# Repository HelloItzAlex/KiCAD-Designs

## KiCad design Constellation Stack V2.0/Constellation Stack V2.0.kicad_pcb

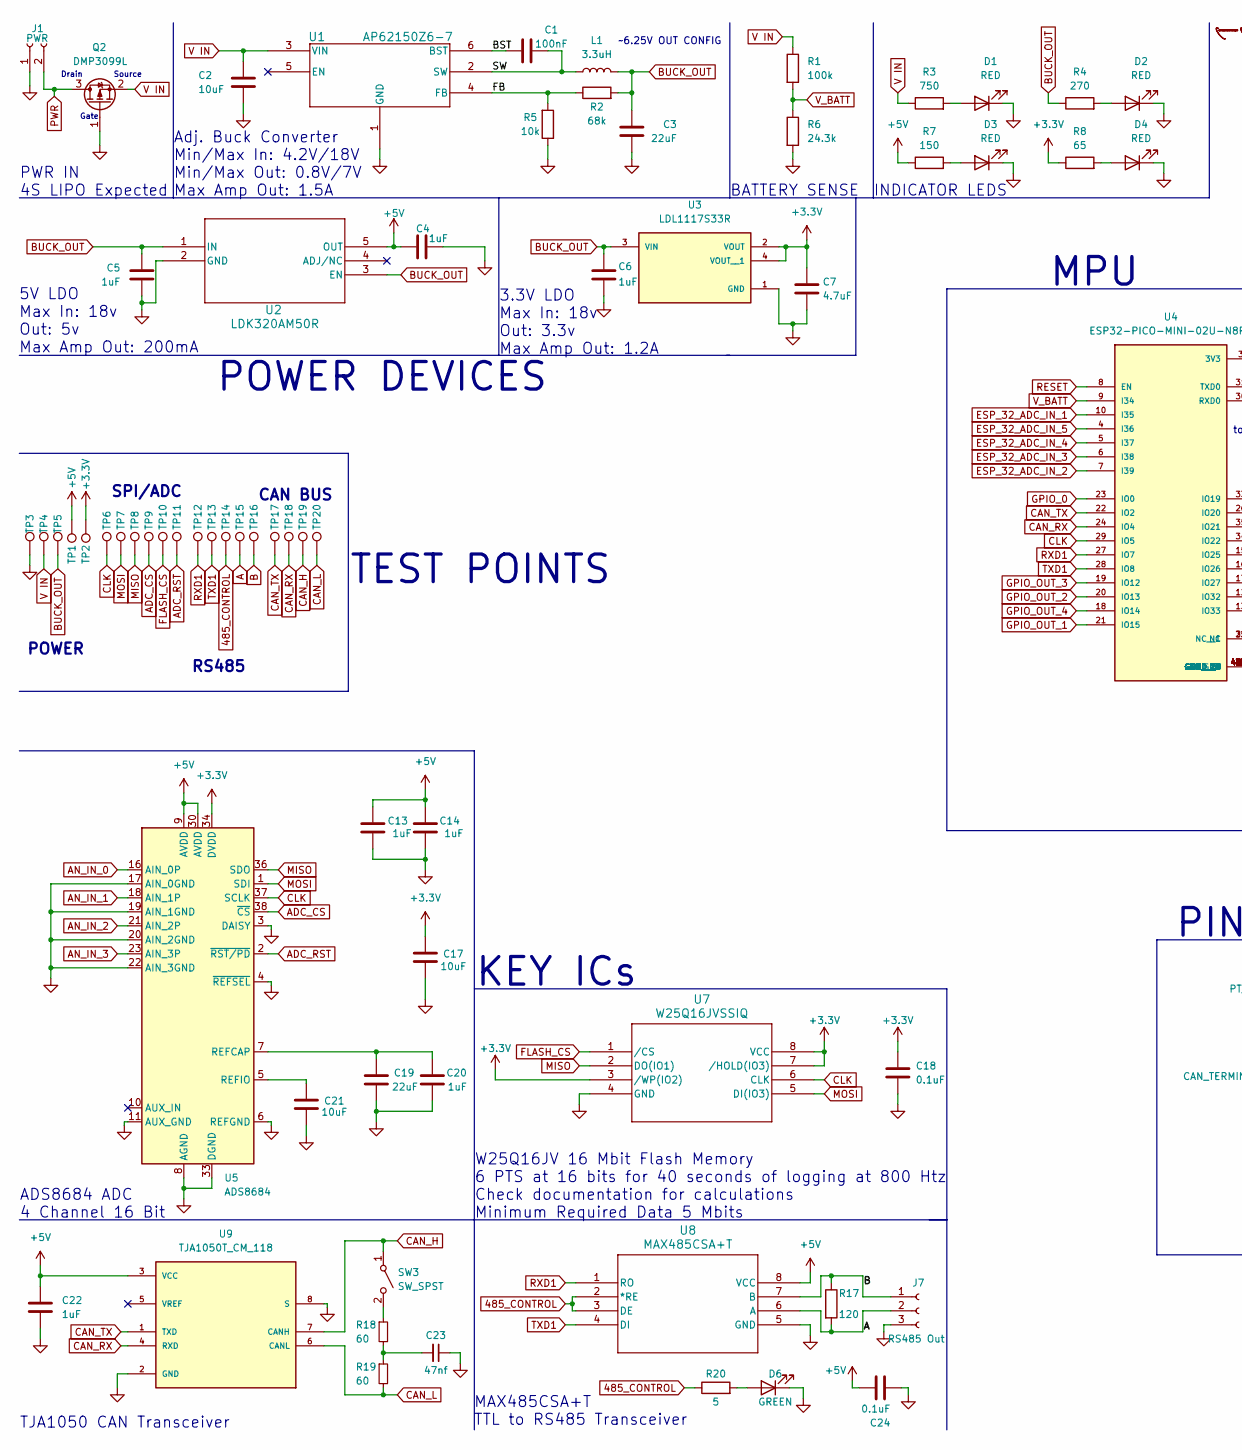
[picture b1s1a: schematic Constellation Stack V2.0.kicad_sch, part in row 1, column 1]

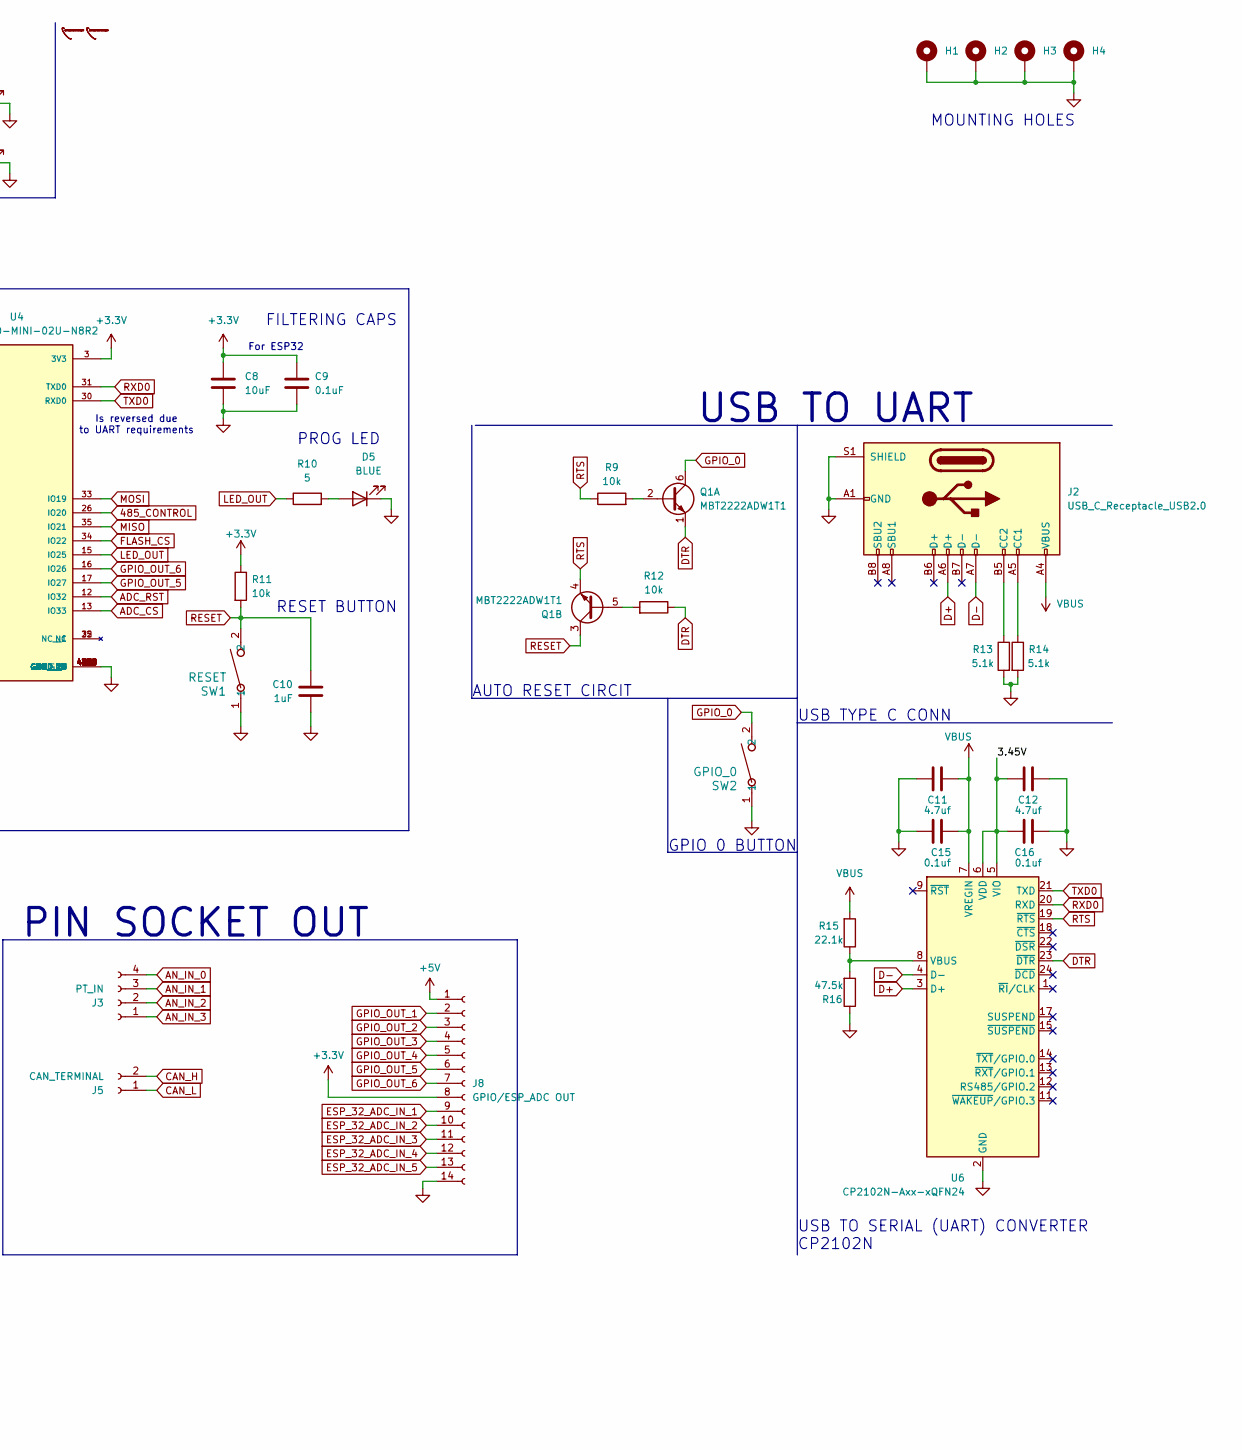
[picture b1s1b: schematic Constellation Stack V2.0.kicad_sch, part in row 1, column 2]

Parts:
C1: 100nF; C_0603_1608Metric
C2, C8, C17: 10uF; C_0805_2012Metric
C3: 22uF; C_0603_1608Metric
C4, C10, C13, C14, C20, C22: 1uF; C_0603_1608Metric
C5, C6: 1uF; C_0805_2012Metric
C7: 4.7uF; C_0603_1608Metric
C9, C18, C24: 0.1uF; C_0603_1608Metric
C11, C12: 4.7uf; C_0603_1608Metric
C15, C16: 0.1uf; C_0603_1608Metric
C19: 22uF; C_1210_3225Metric
C21: 10uF; C_0603_1608Metric
C23: 47nf; C_0603_1608Metric
D1, D2, D3, D4: RED; LED_0603_1608Metric
D5: BLUE; LED_0603_1608Metric
D6: GREEN; LED_0603_1608Metric
H1, H2, H3, H4: MountingHole_Pad; MountingHole_3.2mm_M3_DIN965_Pad
J1: PWR; PinSocket_1x02_P2.54mm_Vertical
J2: USB_C_Receptacle_USB2.0; USB_C_Receptacle_HCTL_HC-TYPE-C-16P-01A
J3: PT_IN; PinSocket_1x04_P2.54mm_Vertical
J5: CAN_TERMINAL; PinSocket_1x02_P2.54mm_Vertical
J7: RS485 Out; PinSocket_1x03_P2.54mm_Vertical
J8: GPIO/ESP_ADC OUT; PinSocket_1x14_P2.54mm_Vertical
L1: 3.3uH; L_1008_2520Metric
Q1: MBT2222ADW1T1; SOT-363_SC-70-6
Q2: DMP3099L; SOT-23-3
R1: 100k; R_0603_1608Metric
R2: 68k; R_0603_1608Metric
R3: 750; R_0603_1608Metric
R4: 270; R_0603_1608Metric
R5, R9, R11, R12: 10k; R_0603_1608Metric
R6: 24.3k; R_0603_1608Metric
R7: 150; R_0603_1608Metric
R8: 65; R_0603_1608Metric
R10, R20: 5; R_0603_1608Metric
R13, R14: 5.1k; R_0603_1608Metric
R15: 22.1k; R_0603_1608Metric
R16: 47.5k; R_0603_1608Metric
R17: 120; R_0805_2012Metric
R18, R19: 60; R_0805_2012Metric
SW1: RESET; SW_PTS636_CNK
SW2: GPIO_0; SW_PTS636_CNK
SW3: SW_SPST; SolderJumper-2_P1.3mm_Open_RoundedPad1.0x1.5mm
TP1, TP2, TP3, TP4, TP5, TP6, TP7, TP8, TP9, TP10, TP11, TP12, TP13, TP14, TP15, TP16, TP17, TP18, TP19, TP20: TestPoint; TestPoint_Loop_D2.60mm_Drill1.6mm_Beaded
U1: AP62150Z6-7; TSOT-23-6
U2: LDK320AM50R; SC-74A-5_1.55x2.9mm_P0.95mm
U3: LDL1117S33R; SOT-223; PARTREV 7
U4: ESP32-PICO-MINI-02U-N8R2; MODULE_ESP32-PICO-MINI-02U-N8R2; PARTREV v1.1
U5: ADS8684; TSSOP-38_4.4x9.7mm_P0.5mm
U6: CP2102N-Axx-xQFN24; QFN-24-1EP_4x4mm_P0.5mm_EP2.7x2.7mm
U7: W25Q16JVSSIQ; SOIC-8_5.275x5.275mm_P1.27mm
U8: MAX485CSA+T; SOIC-8_3.9x4.9mm_P1.27mm
U9: TJA1050T_CM_118; SOIC-8_3.9x4.9mm_P1.27mm; PARTREV 4

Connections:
485_CONTROL: R20.1, TP14.1, U4.26 (IO20), U8.2 (*RE), U8.3 (DE)
+3.3V: C7.1, C8.1, C9.1, C17.2, C18.1, J8.8, R8.1, R11.1, TP2.1, U3.2 (VOUT), U3.4 (VOUT__1), U4.3 (3V3), U5.34 (DVDD), U7.3 (/WP(IO2)), U7.7 (/HOLD(IO3)), U7.8 (VCC)
+5V: C4.1, C13.2, C14.2, C22.1, C24.1, J8.1, R7.1, TP1.1, U2.5 (OUT), U5.9 (AVDD), U5.30 (AVDD), U8.8 (VCC), U9.3 (VCC)
/3.45V: C12.1, C16.1, U6.5 (VIO), U6.6 (VDD)
/BST: C1.1, U1.6 (BST)
/FB: R2.1, R5.2, U1.4 (FB)
/SW: C1.2, L1.1, U1.2 (SW)
A: J7.2, R17.2, TP15.1, U8.6 (A)
ADC_CS: TP9.1, U4.13 (IO33), U5.38 (~CS)
ADC_RST: TP11.1, U4.12 (IO32), U5.2 (~RST/PD)
AN_IN_0: J3.4, U5.16 (AIN_0P)
AN_IN_1: J3.3, U5.18 (AIN_1P)
AN_IN_2: J3.2, U5.21 (AIN_2P)
AN_IN_3: J3.1, U5.23 (AIN_3P)
B: J7.1, R17.1, TP16.1, U8.7 (B)
BUCK_OUT: C3.1, C5.1, C6.1, L1.2, R2.2, R4.1, TP5.1, U2.1 (IN), U2.3 (EN), U3.3 (VIN)
CAN_H: J5.2, SW3.1 (A), TP19.1, U9.7 (CANH)
CAN_L: J5.1, R19.2, TP20.1, U9.6 (CANL)
CAN_RX: TP18.1, U4.24 (IO4), U9.4 (RXD)
CAN_TX: TP17.1, U4.22 (IO2), U9.1 (TXD)
CLK: TP6.1, U4.29 (IO5), U5.37 (SCLK), U7.6 (CLK)
D+: J2.A6 (D+), U6.3 (D+)
D-: J2.A7 (D-), U6.4 (D-)
DTR: Q1.1 (E1), R12.1, U6.23 (~DTR)
ESP_32_ADC_IN_1: J8.9, U4.10 (I35)
ESP_32_ADC_IN_2: J8.10, U4.7 (I39)
ESP_32_ADC_IN_3: J8.11, U4.6 (I38)
ESP_32_ADC_IN_4: J8.12, U4.5 (I37)
ESP_32_ADC_IN_5: J8.13, U4.4 (I36)
FLASH_CS: TP10.1, U4.34 (IO22), U7.1 (/CS)
GND: C2.2, C3.2, C4.2, C5.2, C6.2, C7.2, C8.2, C9.2, C10.2, C11.2, C12.2, C13.1, C14.1, C15.2, C16.2, C17.1, C18.2, C19.1, C20.1, C21.2, C22.2, C23.1, C24.2, D1.1 (K), D2.1 (K), D3.1 (K), D4.1 (K), D5.1 (K), D6.1 (K), H1.1, H2.1, H3.1, H4.1, J1.1, J2.A1 (GND), J2.A12 (GND), J2.B1 (GND), J2.B12 (GND), J2.S1 (SHIELD), J7.3, J8.14, Q2.1 (G), R5.1, R6.2, R13.2, R14.2, R16.1, SW1.1, SW2.1, TP3.1, U1.1 (GND), U2.2 (GND), U3.1 (GND), U4.1 (GND), U4.2 (GND__1), U4.11 (GND__2), U4.14 (GND__3), U4.36 (GND__4), U4.37 (GND__5), U4.38 (GND__6), U4.39 (GND__7), U4.40 (GND__8), U4.41 (GND__9), U4.42 (GND__10), U4.43 (GND__11), U4.44 (GND__12), U4.45 (GND__13), U4.46 (GND__14), U4.47 (GND__15), U4.48 (GND__16), U4.49_1 (GND__17), U4.49_2 (GND__18), U4.49_3 (GND__19), U4.49_4 (GND__20), U4.49_5 (GND__21), U4.49_6 (GND__22), U4.49_7 (GND__23), U4.49_8 (GND__24), U4.49_9 (GND__25), U4.50 (GND__26), U4.51 (GND__27), U4.52 (GND__28), U4.53 (GND__29), U5.3 (DAISY), U5.4 (~REFSEL), U5.6 (REFGND), U5.8 (AGND), U5.11 (AUX_GND), U5.17 (AIN_0GND), U5.19 (AIN_1GND), U5.20 (AIN_2GND), U5.22 (AIN_3GND), U5.28 (AGND), U5.29 (AGND), U5.31 (AGND), U5.32 (AGND), U5.33 (DGND), U6.2 (GND), U6.25 (GND), U7.4 (GND), U8.5 (GND), U9.2 (GND), U9.8 (S)
GPIO_0: Q1.6 (C1), SW2.2, U4.23 (IO0)
GPIO_OUT_1: J8.2, U4.21 (IO15)
GPIO_OUT_2: J8.3, U4.20 (IO13)
GPIO_OUT_3: J8.4, U4.19 (IO12)
GPIO_OUT_4: J8.5, U4.18 (IO14)
GPIO_OUT_5: J8.6, U4.17 (IO27)
GPIO_OUT_6: J8.7, U4.16 (IO26)
LED_OUT: R10.1, U4.15 (IO25)
MISO: TP8.1, U4.35 (IO21), U5.36 (SDO), U7.2 (DO(IO1))
MOSI: TP7.1, U4.33 (IO19), U5.1 (SDI), U7.5 (DI(IO3))
unnamed: C23.2, R18.2, R19.1
unnamed: D1.2 (A), R3.2
unnamed: D2.2 (A), R4.2
unnamed: D3.2 (A), R7.2
unnamed: D4.2 (A), R8.2
unnamed: D5.2 (A), R10.2
unnamed: D6.2 (A), R20.2
unnamed: J2.A5 (CC1), R14.1
unnamed: J2.B5 (CC2), R13.1
unnamed: Q1.2 (B1), R9.2
unnamed: Q1.5 (B2), R12.2
unnamed: R18.1, SW3.2 (B)
unnamed: C19.2, C20.2, U5.7 (REFCAP)
unnamed: C21.1, U5.5 (REFIO)
unnamed: R15.1, R16.2, U6.8 (VBUS)
PWR: J1.2, Q2.3 (D)
RESET: C10.1, Q1.3 (C2), R11.2, SW1.2, U4.8 (EN)
RTS: Q1.4 (E2), R9.1, U6.19 (~RTS)
RXD0: U4.31 (TXD0), U6.20 (RXD)
RXD1: TP12.1, U4.27 (IO7), U8.1 (RO)
TXD0: U4.30 (RXD0), U6.21 (TXD)
TXD1: TP13.1, U4.28 (IO8), U8.4 (DI)
V IN: C2.1, Q2.2 (S), R1.1, R3.1, TP4.1, U1.3 (VIN)
VBUS: C11.1, C15.1, J2.A4 (VBUS), J2.A9 (VBUS), J2.B4 (VBUS), J2.B9 (VBUS), R15.2, U6.7 (VREGIN)
V_BATT: R1.2, R6.1, U4.9 (I34)

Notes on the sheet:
SPI/ADC
INDICATOR LEDS
POWER DEVICES
USB TO SERIAL (UART) CONVERTER CP2102N
CAN BUS
Source
MAX485CSA+T TTL to RS485 Transceiver
PROG LED
Adj. Buck Converter Min/Max In: 4.2V/18V Min/Max Out: 0.8V/7V Max Amp Out: 1.5A
POWER
TEST POINTS
3.3V LDO Max In: 18v Out: 3.3v Max Amp Out: 1.2A
Gate
FILTERING CAPS
MOUNTING HOLES
~6.25V OUT CONFIG
USB TYPE C CONN
ADS8684 ADC 4 Channel 16 Bit
KEY ICs
TJA1050 CAN Transceiver
PWR IN 4S LIPO Expected
AUTO RESET CIRCIT
Drain
5V LDO Max In: 18v Out: 5v Max Amp Out: 200mA
W25Q16JV 16 Mbit Flash Memory 6 PTS at 16 bits for 40 seconds of logging at 800 Htz Check documentation for calculations Minimum Required Data 5 Mbits
For ESP32
BATTERY SENSE
PIN SOCKET OUT
Is reversed due to UART requirements
GPIO 0 BUTTON
MPU
RESET BUTTON
USB TO UART
RS485

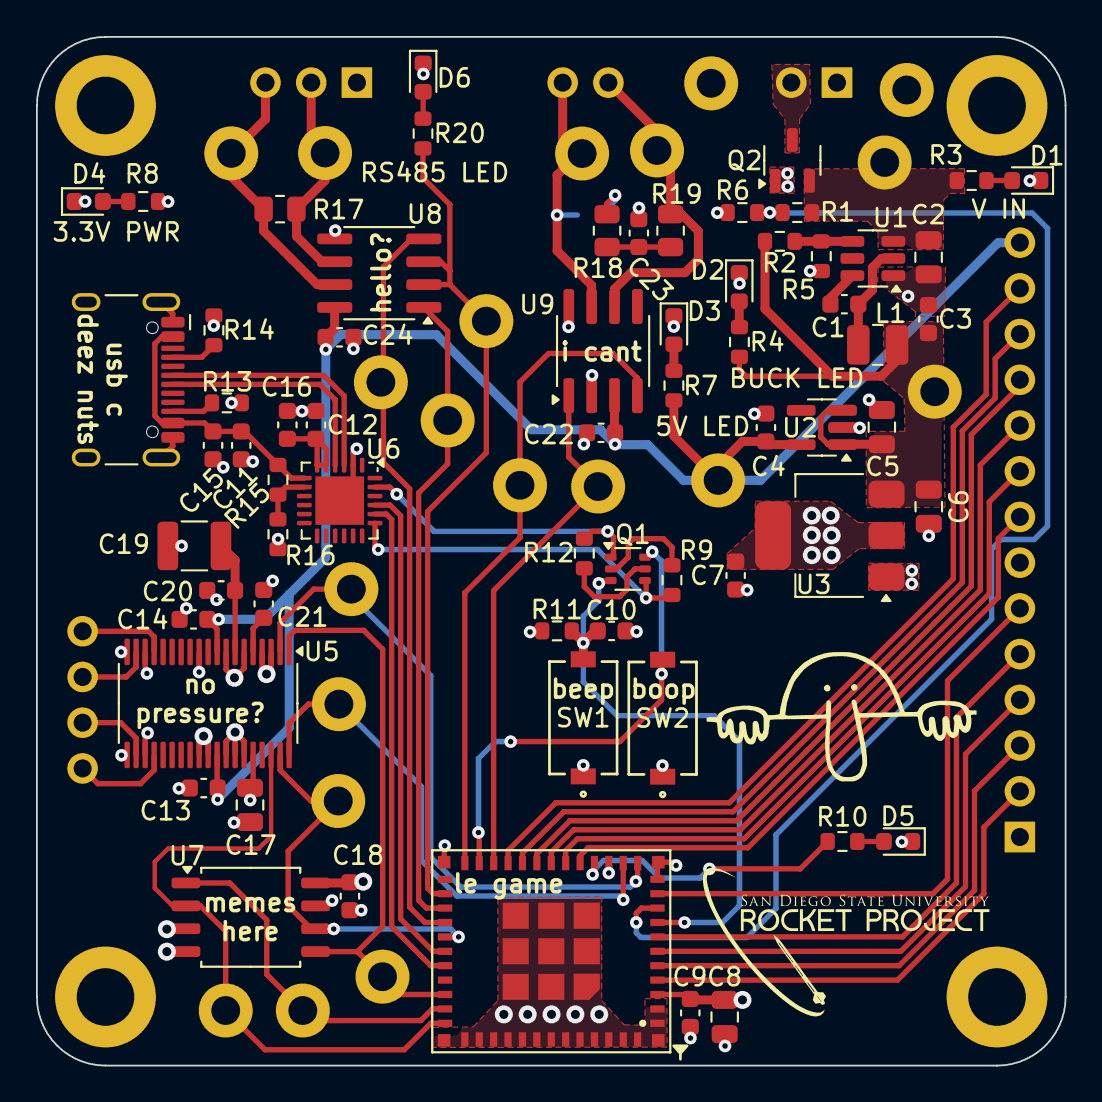
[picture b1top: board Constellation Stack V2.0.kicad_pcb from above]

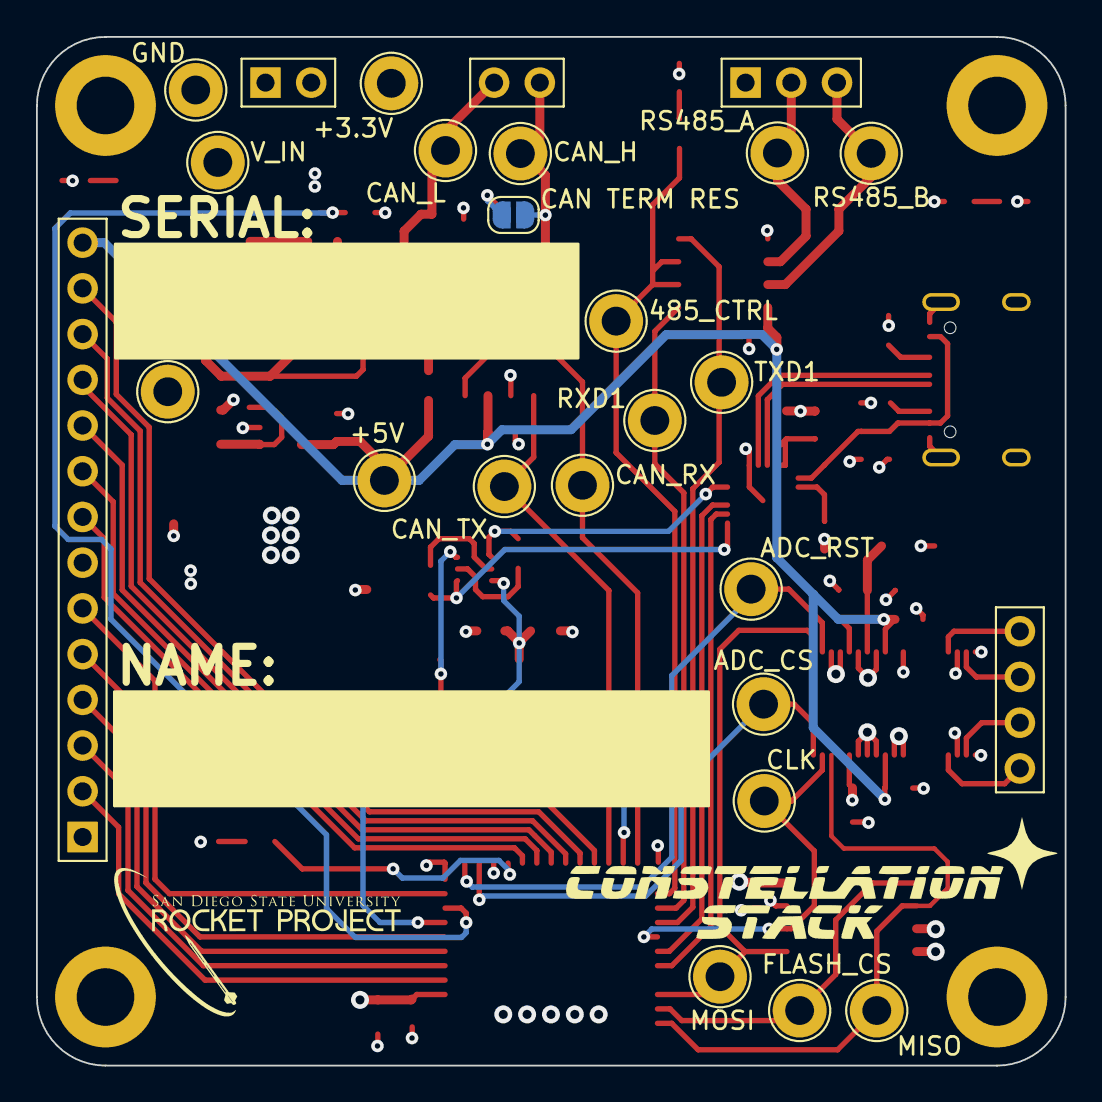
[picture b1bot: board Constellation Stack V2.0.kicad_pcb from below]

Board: 4 copper layers, 57.1 x 57.1 mm, 95 parts (26 on the bottom side), 66 nets.

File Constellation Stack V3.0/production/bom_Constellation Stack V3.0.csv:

Designator,Footprint,Quantity,Value,LCSC Part #
"C1, C11, C12, C15, C16",603,5,100nF,C24452
"C10, C13, C14, C20, C4",603,5,1uF,C59782
"C17, C2, C8",805,3,10uF,C3039694
"C18, C23, C24, C9",603,4,0.1uF,C24452
C19,1210,1,22uF,C55530
"C21, C22",603,2,10uF,C92487
C3,805,1,22uF,C602037
"C5, C6",805,2,1uF,C1712
C7,603,1,4.7uF,C107368
CR1,DO-214BA_MCH-L,1,LSM115JE3/TR13,C3757764
"D1, D2, D3, D4",603,4,RED,C3030991
D5,603,1,BLUE,C5197644
D6,603,1,GREEN,C5252984
L1,1008,1,3.3uH,C337916
Q2,SOT-23-3,1,DMP3099L,C155244
"R10, R20",603,2,5,C227988
"R11, R5",603,2,10k,C98220
R17,805,1,120,C114245
R2,603,1,68k,C114633
R3,603,1,750,C114635
R4,603,1,270,C137754
R7,603,1,150,C114608
R8,603,1,65,C273751
U1,TSOT-23-6,1,AP62150Z6-7,C3194237
U10,TSSOP-38_4.4x9.7mm_P0.5mm,1,ADS8688,C527390
U2,SC-74A-5_1.55x2.9mm_P0.95mm,1,LDK320AM50R,C2969843
U3,SOT-223,1,LDL1117S33R,C435835
U4,10LGA_2X2X0p75_BOS,1,BMP390,C2684802
U5,ESP32-WROOM-32UE,1,ESP32-WROOM-32UE,C701346
U6,BMI088,1,BMI088,C194919
U7,SOIC-8_5.275x5.275mm_P1.27mm,1,W25Q16JVSSIQ,C82317
U8,SOIC-8_3.9x4.9mm_P1.27mm,1,MAX485CSA+T,C9945
U9,SOT-23-5,1,MIC5504-3.3YM5,C88419

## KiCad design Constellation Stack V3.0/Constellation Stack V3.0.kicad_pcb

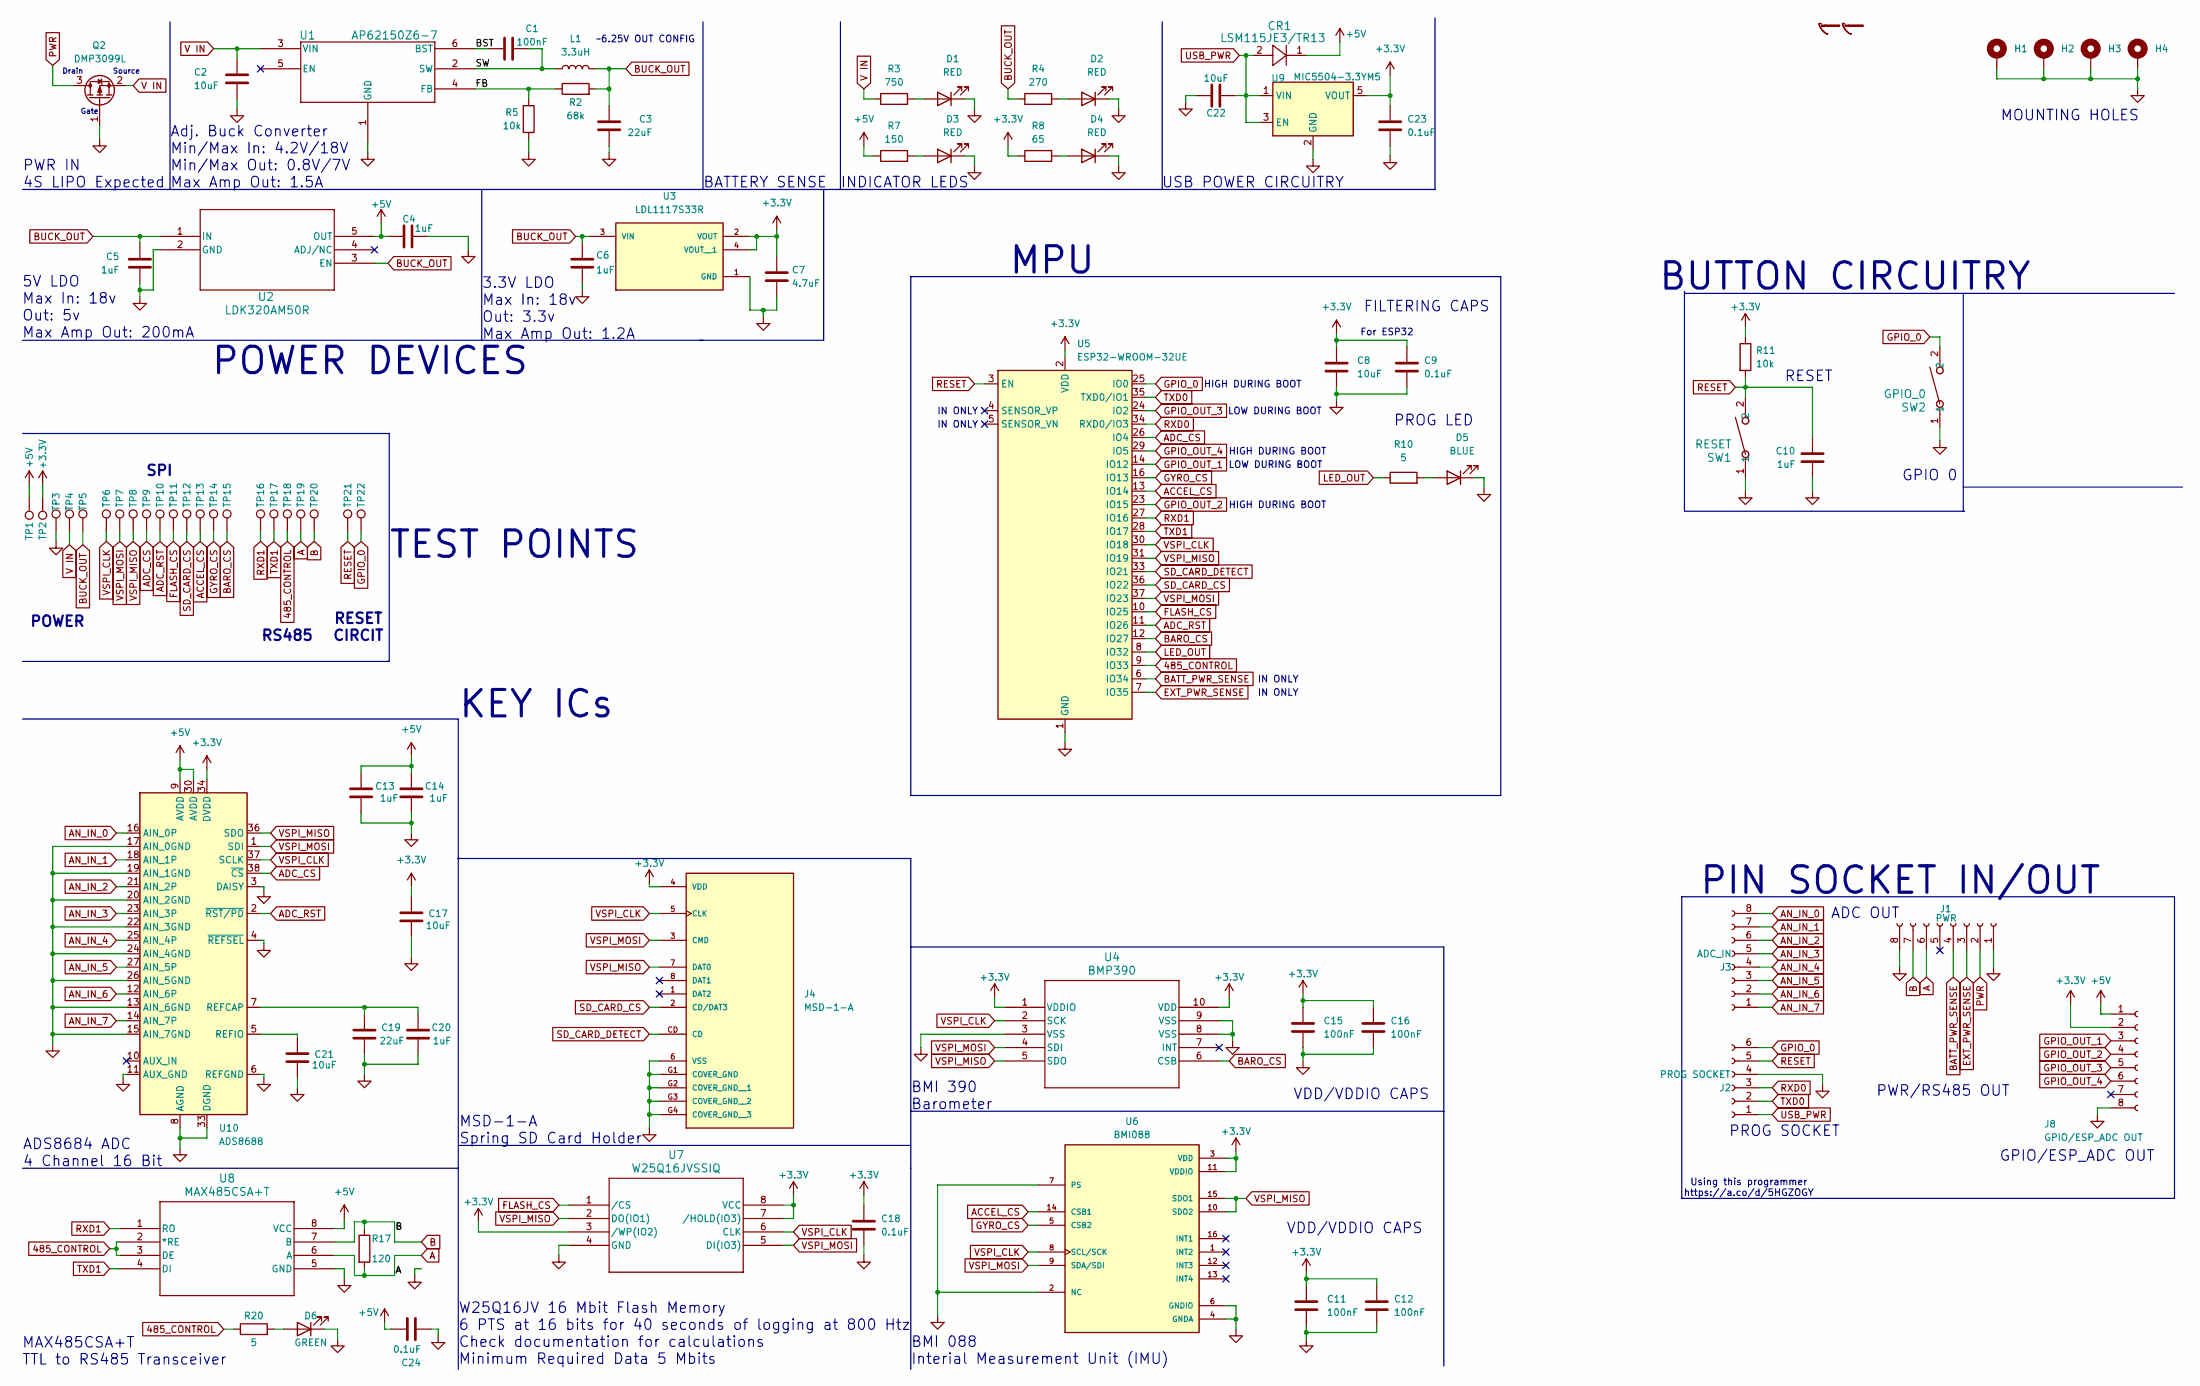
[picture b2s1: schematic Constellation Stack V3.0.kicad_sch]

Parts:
C1, C11, C12, C15, C16: 100nF; C_0603_1608Metric
C2, C8, C17: 10uF; C_0805_2012Metric
C3: 22uF; C_0805_2012Metric
C4, C10, C13, C14, C20: 1uF; C_0603_1608Metric
C5, C6: 1uF; C_0805_2012Metric
C7: 4.7uF; C_0603_1608Metric
C9, C18, C23, C24: 0.1uF; C_0603_1608Metric
C19: 22uF; C_1210_3225Metric
C21, C22: 10uF; C_0603_1608Metric
CR1: LSM115JE3/TR13; DO-214BA_MCH-L
D1, D2, D3, D4: RED; LED_0603_1608Metric
D5: BLUE; LED_0603_1608Metric
D6: GREEN; LED_0603_1608Metric
H1, H2, H3, H4: MountingHole_Pad; MountingHole_3.2mm_M3_DIN965_Pad
J1: PWR; PinSocket_1x08_P2.54mm_Vertical
J2: PROG SOCKET; PinSocket_1x06_P2.54mm_Vertical
J3: ADC_IN; PinSocket_1x08_P2.54mm_Vertical
J4: MSD-1-A; CUI_MSD-1-A; PARTREV 1.0
J8: GPIO/ESP_ADC OUT; PinSocket_1x08_P2.54mm_Vertical
L1: 3.3uH; L_1008_2520Metric
Q2: DMP3099L; SOT-23-3
R2: 68k; R_0603_1608Metric
R3: 750; R_0603_1608Metric
R4: 270; R_0603_1608Metric
R5, R11: 10k; R_0603_1608Metric
R7: 150; R_0603_1608Metric
R8: 65; R_0603_1608Metric
R10, R20: 5; R_0603_1608Metric
R17: 120; R_0805_2012Metric
SW1: RESET; SW_PTS636_CNK
SW2: GPIO_0; SW_PTS636_CNK
TP1, TP2, TP3, TP4, TP5, TP9, TP10, TP11, TP12, TP13, TP14, TP15, TP18, TP21, TP22: TestPoint; TestPoint_Pad_D1.5mm
TP6, TP7, TP8, TP16, TP17, TP19, TP20: TestPoint; TestPoint_Loop_D2.60mm_Drill1.6mm_Beaded
U1: AP62150Z6-7; TSOT-23-6
U2: LDK320AM50R; SC-74A-5_1.55x2.9mm_P0.95mm
U3: LDL1117S33R; SOT-223; PARTREV 7
U4: BMP390; 10LGA_2X2X0p75_BOS
U5: ESP32-WROOM-32UE
U6: BMI088; DigiKey_Part_Number 828-1082-2-ND
U7: W25Q16JVSSIQ; SOIC-8_5.275x5.275mm_P1.27mm
U8: MAX485CSA+T; SOIC-8_3.9x4.9mm_P1.27mm
U9: MIC5504-3.3YM5; SOT-23-5
U10: ADS8688; TSSOP-38_4.4x9.7mm_P0.5mm

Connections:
485_CONTROL: R20.1, TP18.1, U5.9 (IO33), U8.2 (*RE), U8.3 (DE)
+3.3V: C7.1, C8.1, C9.1, C11.1, C12.1, C15.1, C16.1, C17.2, C18.1, C23.1, J4.4 (VDD), J8.2, R8.1, R11.1, TP2.1, U3.2 (VOUT), U3.4 (VOUT__1), U4.1 (VDDIO), U4.10 (VDD), U5.2 (VDD), U6.3 (VDD), U6.11 (VDDIO), U7.3 (/WP(IO2)), U7.7 (/HOLD(IO3)), U7.8 (VCC), U9.5 (VOUT), U10.34 (DVDD)
+5V: C4.1, C13.2, C14.2, C24.1, CR1.1, J8.1, R7.1, TP1.1, U2.5 (OUT), U8.8 (VCC), U10.9 (AVDD), U10.30 (AVDD)
/BST: C1.1, U1.6 (BST)
/FB: R2.1, R5.2, U1.4 (FB)
/SW: C1.2, L1.1, U1.2 (SW)
A: J1.6, R17.2, TP19.1, U8.6 (A)
ACCEL_CS: TP13.1, U5.13 (IO14), U6.14 (CSB1)
ADC_CS: TP9.1, U5.26 (IO4), U10.38 (~CS)
ADC_RST: TP10.1, U5.11 (IO26), U10.2 (~RST/PD)
AN_IN_0: J3.8, U10.16 (AIN_0P)
AN_IN_1: J3.7, U10.18 (AIN_1P)
AN_IN_2: J3.6, U10.21 (AIN_2P)
AN_IN_3: J3.5, U10.23 (AIN_3P)
AN_IN_4: J3.4, U10.25 (AIN_4P)
AN_IN_5: J3.3, U10.27 (AIN_5P)
AN_IN_6: J3.2, U10.12 (AIN_6P)
AN_IN_7: J3.1, U10.14 (AIN_7P)
B: J1.7, R17.1, TP20.1, U8.7 (B)
BARO_CS: TP15.1, U4.6 (CSB), U5.12 (IO27)
BATT_PWR_SENSE: J1.4, U5.6 (IO34)
BUCK_OUT: C3.1, C5.1, C6.1, L1.2, R2.2, R4.1, TP5.1, U2.1 (IN), U2.3 (EN), U3.3 (VIN)
EXT_PWR_SENSE: J1.3, U5.7 (IO35)
FLASH_CS: TP11.1, U5.10 (IO25), U7.1 (/CS)
GND: C2.2, C3.2, C4.2, C5.2, C6.2, C7.2, C8.2, C9.2, C10.2, C11.2, C12.2, C13.1, C14.1, C15.2, C16.2, C17.1, C18.2, C19.1, C20.1, C21.2, C22.1, C23.2, C24.2, D1.1 (K), D2.1 (K), D3.1 (K), D4.1 (K), D5.1 (K), D6.1 (K), H1.1, H2.1, H3.1, H4.1, J1.1, J1.8, J2.4, J4.6 (VSS), J4.G1 (COVER_GND), J4.G2 (COVER_GND__1), J4.G3 (COVER_GND__2), J4.G4 (COVER_GND__3), J8.8, Q2.1 (G), R5.1, SW1.1, SW2.1, TP3.1, U1.1 (GND), U2.2 (GND), U3.1 (GND), U4.3 (VSS), U4.8 (VSS), U4.9 (VSS), U5.1 (GND), U5.15 (GND), U5.38 (GND), U5.39 (GND), U6.2 (NC), U6.4 (GNDA), U6.6 (GNDIO), U6.7 (PS), U7.4 (GND), U8.5 (GND), U9.2 (GND), U10.3 (DAISY), U10.4 (~REFSEL), U10.6 (REFGND), U10.8 (AGND), U10.11 (AUX_GND), U10.13 (AIN_6GND), U10.15 (AIN_7GND), U10.17 (AIN_0GND), U10.19 (AIN_1GND), U10.20 (AIN_2GND), U10.22 (AIN_3GND), U10.24 (AIN_4GND), U10.26 (AIN_5GND), U10.28 (AGND), U10.29 (AGND), U10.31 (AGND), U10.32 (AGND), U10.33 (DGND)
GPIO_0: J2.6, SW2.2, TP22.1, U5.25 (IO0)
GPIO_OUT_1: J8.3, U5.14 (IO12)
GPIO_OUT_2: J8.4, U5.23 (IO15)
GPIO_OUT_3: J8.5, U5.24 (IO2)
GPIO_OUT_4: J8.6, U5.29 (IO5)
GYRO_CS: TP14.1, U5.16 (IO13), U6.5 (CSB2)
LED_OUT: R10.1, U5.8 (IO32)
unnamed: D1.2 (A), R3.2
unnamed: D2.2 (A), R4.2
unnamed: D3.2 (A), R7.2
unnamed: D4.2 (A), R8.2
unnamed: D5.2 (A), R10.2
unnamed: D6.2 (A), R20.2
unnamed: C19.2, C20.2, U10.7 (REFCAP)
unnamed: C21.1, U10.5 (REFIO)
PWR: J1.2, Q2.3 (D)
RESET: C10.1, J2.5, R11.2, SW1.2, TP21.1, U5.3 (EN)
RXD0: J2.3, U5.34 (RXD0/IO3)
RXD1: TP16.1, U5.27 (IO16), U8.1 (RO)
SD_CARD_CS: J4.2 (CD/DAT3), TP12.1, U5.36 (IO22)
SD_CARD_DETECT: J4.CD, U5.33 (IO21)
TXD0: J2.2, U5.35 (TXD0/IO1)
TXD1: TP17.1, U5.28 (IO17), U8.4 (DI)
USB_PWR: C22.2, CR1.2, J2.1, U9.1 (VIN), U9.3 (EN)
V IN: C2.1, Q2.2 (S), R3.1, TP4.1, U1.3 (VIN)
VSPI_CLK: J4.5 (CLK), TP6.1, U4.2 (SCK), U5.30 (IO18), U6.8 (SCL/SCK), U7.6 (CLK), U10.37 (SCLK)
VSPI_MISO: J4.7 (DAT0), TP8.1, U4.5 (SDO), U5.31 (IO19), U6.10 (SDO2), U6.15 (SDO1), U7.2 (DO(IO1)), U10.36 (SDO)
VSPI_MOSI: J4.3 (CMD), TP7.1, U4.4 (SDI), U5.37 (IO23), U6.9 (SDA/SDI), U7.5 (DI(IO3)), U10.1 (SDI)

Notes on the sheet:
IN ONLY
MSD-1-A Spring SD Card Holder
HIGH DURING BOOT
SPI
INDICATOR LEDS
POWER DEVICES
USB POWER CIRCUITRY
Source
LOW DURING BOOT
MAX485CSA+T TTL to RS485 Transceiver
PROG LED
Adj. Buck Converter Min/Max In: 4.2V/18V Min/Max Out: 0.8V/7V Max Amp Out: 1.5A
RESET CIRCIT
POWER
TEST POINTS
3.3V LDO Max In: 18v Out: 3.3v Max Amp Out: 1.2A
Gate
FILTERING CAPS
MOUNTING HOLES
~6.25V OUT CONFIG
PROG SOCKET
ADS8684 ADC 4 Channel 16 Bit
KEY ICs
ADC OUT
PWR IN 4S LIPO Expected
Drain
PWR/RS485 OUT
5V LDO Max In: 18v Out: 5v Max Amp Out: 200mA
W25Q16JV 16 Mbit Flash Memory 6 PTS at 16 bits for 40 seconds of logging at 800 Htz Check documentation for calculations Minimum Required Data 5 Mbits
Using this programmer https://a.co/d/5HGZOGY
For ESP32
BATTERY SENSE
VDD/VDDIO CAPS
PIN SOCKET IN/OUT
BMI 088 Interial Measurement Unit (IMU)
GPIO 0
GPIO/ESP_ADC OUT
BMI 390 Barometer
MPU
RESET

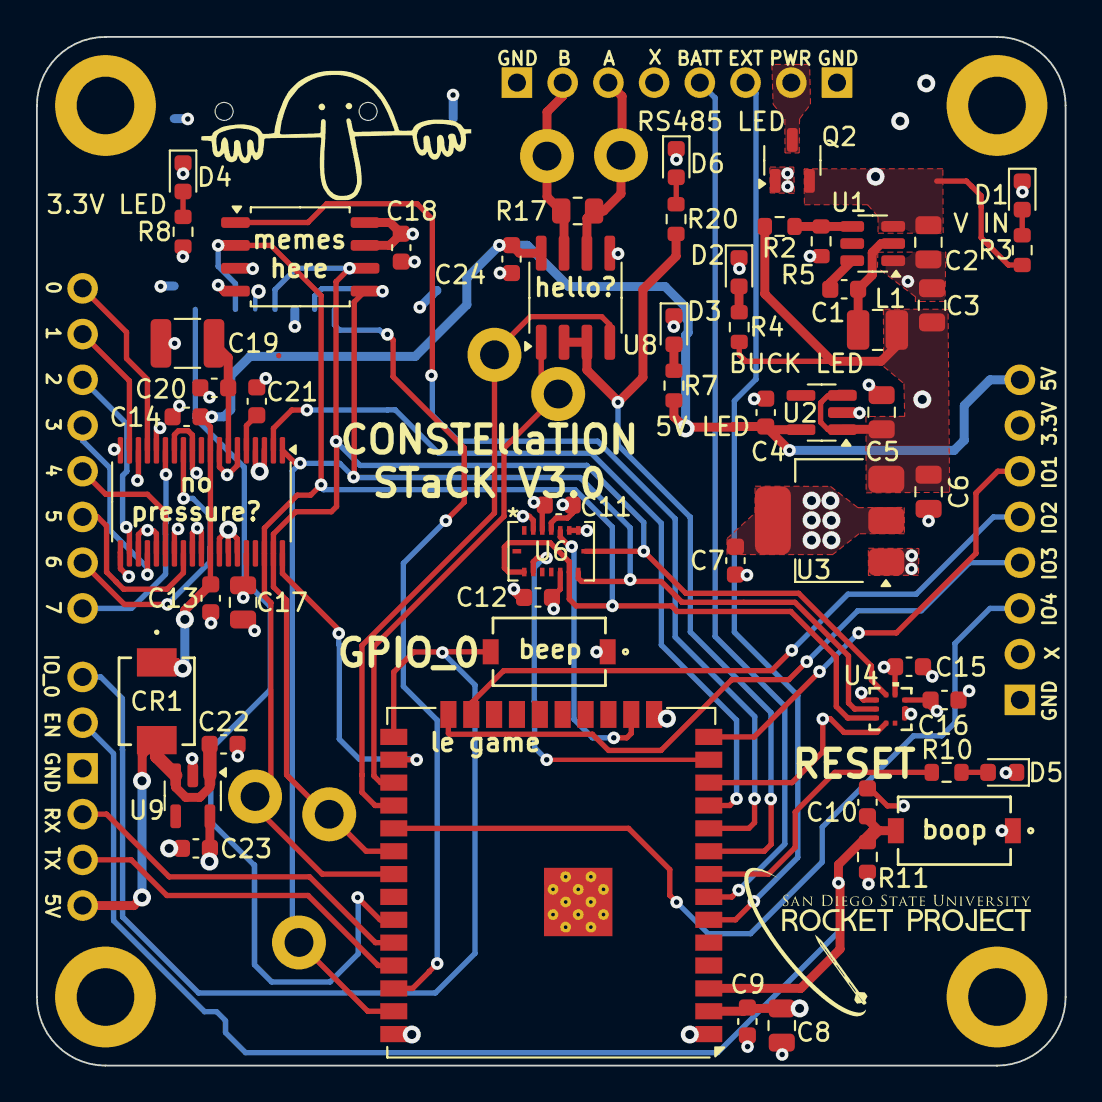
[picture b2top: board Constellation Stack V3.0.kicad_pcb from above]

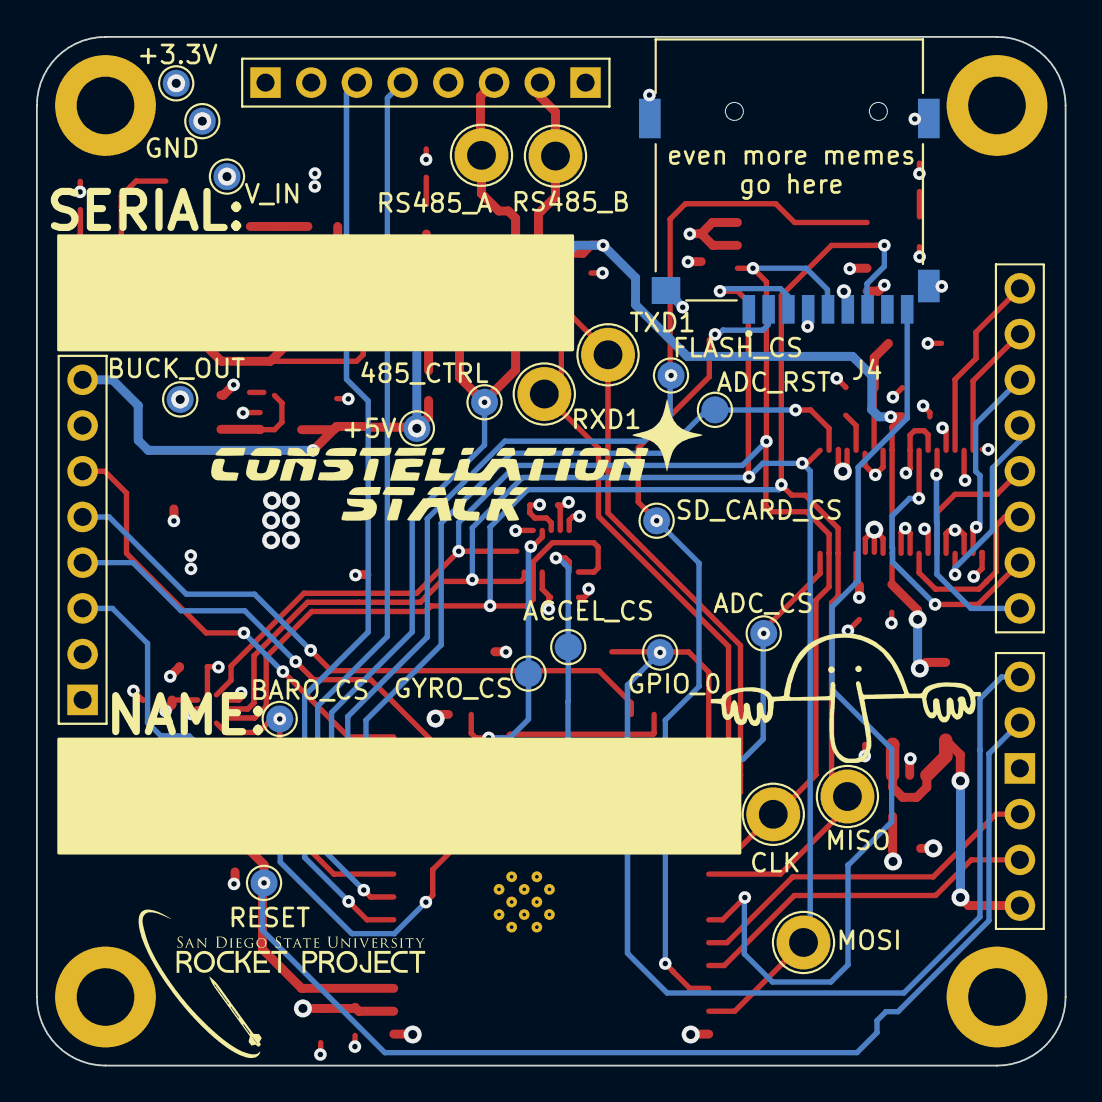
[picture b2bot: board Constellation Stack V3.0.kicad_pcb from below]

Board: 4 copper layers, 57.1 x 57.1 mm, 86 parts (27 on the bottom side), 53 nets.

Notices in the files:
parts and their libraries:
Copyright 2021 Accelerated Designs. All rights reserved.
